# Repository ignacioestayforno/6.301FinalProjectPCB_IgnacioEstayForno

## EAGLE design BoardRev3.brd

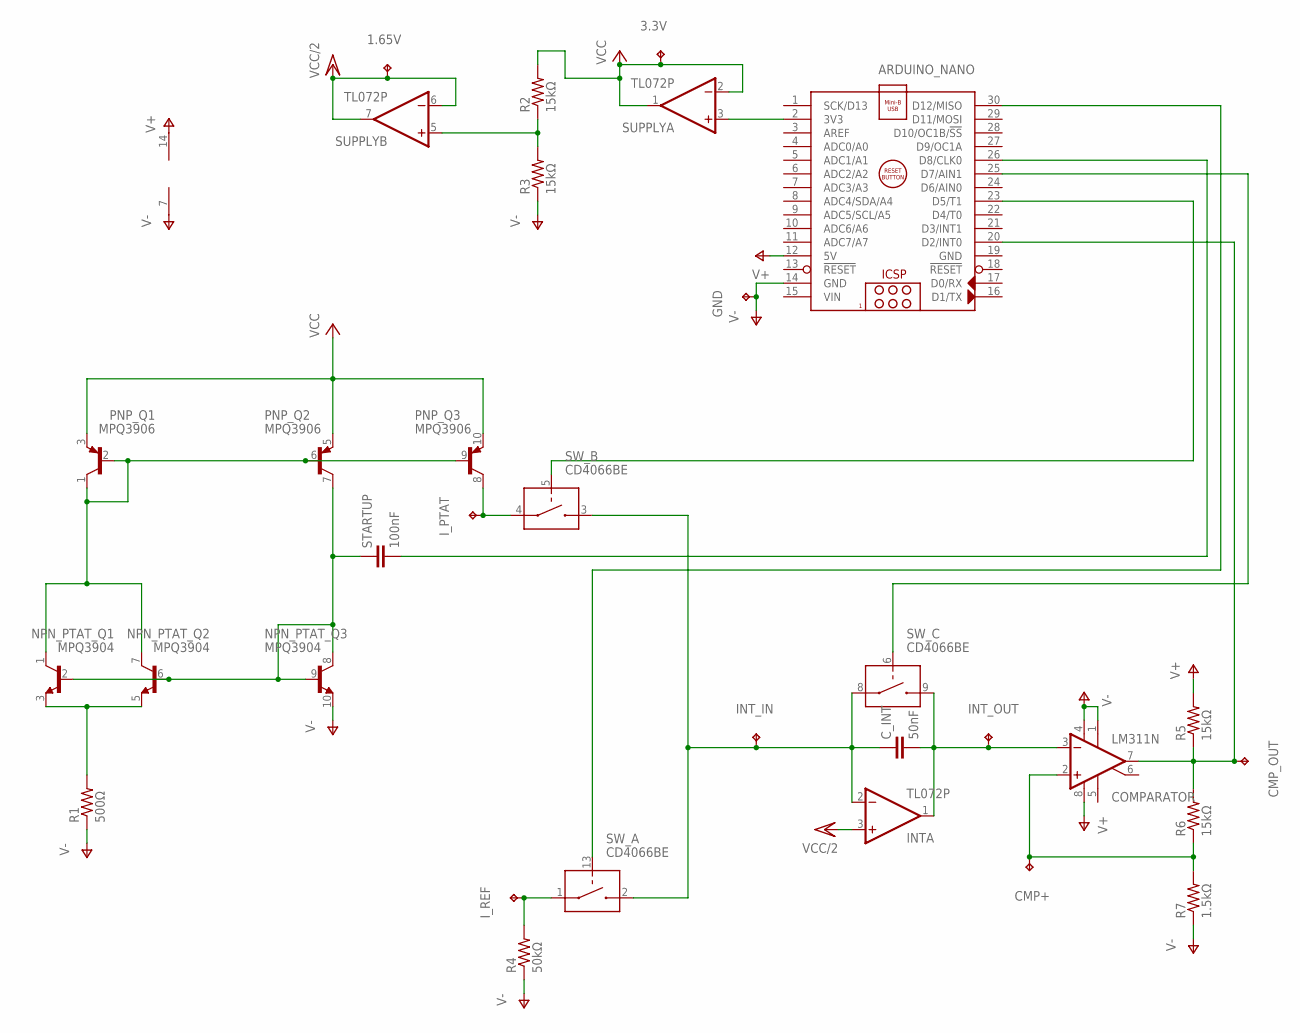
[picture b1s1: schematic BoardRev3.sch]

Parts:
1.65V, 3.3V: TESTPOINT; KEYSTONE_5000_MINIATURE
ARDUINO_NANO: ARDUINO_NANO
CMP+: TESTPOINT; KEYSTONE_5000_MINIATURE
CMP_OUT: TESTPOINT; KEYSTONE_5000_MINIATURE
COMPARATOR: LM311N; DIL08
C_INT: 50nF; C025-025X050
GND: TESTPOINT; KEYSTONE_5000_MINIATURE
INT: TL072P; DIL08
INT_IN: TESTPOINT; KEYSTONE_5000_MINIATURE
INT_OUT: TESTPOINT; KEYSTONE_5000_MINIATURE
I_PTAT: TESTPOINT; KEYSTONE_5000_MINIATURE
I_REF: TESTPOINT; KEYSTONE_5000_MINIATURE
NPN_PTAT: MPQ3904; DIL14
PNP: MPQ3906; DIL14
R1: 500Ω; 0207/10
R2, R3, R5, R6: 15kΩ; 0207/10
R4: 50kΩ; 0207/10
R7: 1.5kΩ; 0207/10
STARTUP: 100nF; C050-030X075
SUPPLY: TL072P; DIL08
SW: CD4066BE; DIL14

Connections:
+3V3: 3.3V.P$1, PNP.3 (E), PNP.5 (E), PNP.10 (E), R2.2, SUPPLY.1 (OUT), SUPPLY.2 (-IN)
GND: ARDUINO_NANO.19 (GND)
unnamed: ARDUINO_NANO.26 (D8/CLK0), STARTUP.2
unnamed: NPN_PTAT.1 (C), NPN_PTAT.7 (C), PNP.1 (C), PNP.2 (B), PNP.6 (B), PNP.9 (B)
unnamed: NPN_PTAT.3 (E), NPN_PTAT.5 (E), R1.2
unnamed: ARDUINO_NANO.2 (3V3), SUPPLY.3 (+IN)
unnamed: NPN_PTAT.2 (B), NPN_PTAT.6 (B), NPN_PTAT.8 (C), NPN_PTAT.9 (B), PNP.7 (C), STARTUP.1
unnamed: CMP+.P$1, COMPARATOR.2 (+IN), R6.1, R7.2
unnamed: R2.1, R3.2, SUPPLY.5 (+IN)
unnamed: ARDUINO_NANO.20 (D2/INT0), CMP_OUT.P$1, COMPARATOR.7 (OUT), R5.1, R6.2
unnamed: C_INT.1, INT.2 (-IN), INT_IN.P$1, SW.2 (IN/OUT2), SW.3 (IN/OUT2), SW.8 (IN/OUT1)
unnamed: COMPARATOR.3 (-IN), C_INT.2, INT.1 (OUT), INT_OUT.P$1, SW.9 (IN/OUT2)
unnamed: I_PTAT.P$1, PNP.8 (C), SW.4 (IN/OUT1)
unnamed: ARDUINO_NANO.30 (D12/MISO), SW.13 (CONTROL)
unnamed: I_REF.P$1, R4.2, SW.1 (IN/OUT1)
unnamed: ARDUINO_NANO.23 (D5/T1), SW.5 (CONTROL)
unnamed: ARDUINO_NANO.25 (D7/AIN1), SW.6 (CONTROL)
V+: ARDUINO_NANO.12 (5V), COMPARATOR.8 (V+), INT.8 (V+), R5.2, SUPPLY.8 (V+), SW.14 (V+)
V-: ARDUINO_NANO.14 (GND), COMPARATOR.1 (GND), COMPARATOR.4 (V-), GND.P$1, INT.4 (V-), NPN_PTAT.10 (E), R1.1, R3.1, R4.1, R7.1, SUPPLY.4 (V-), SW.7 (V-)
VCC/2: 1.65V.P$1, INT.3 (+IN), SUPPLY.6 (-IN), SUPPLY.7 (OUT)
VIN: ARDUINO_NANO.15 (VIN)

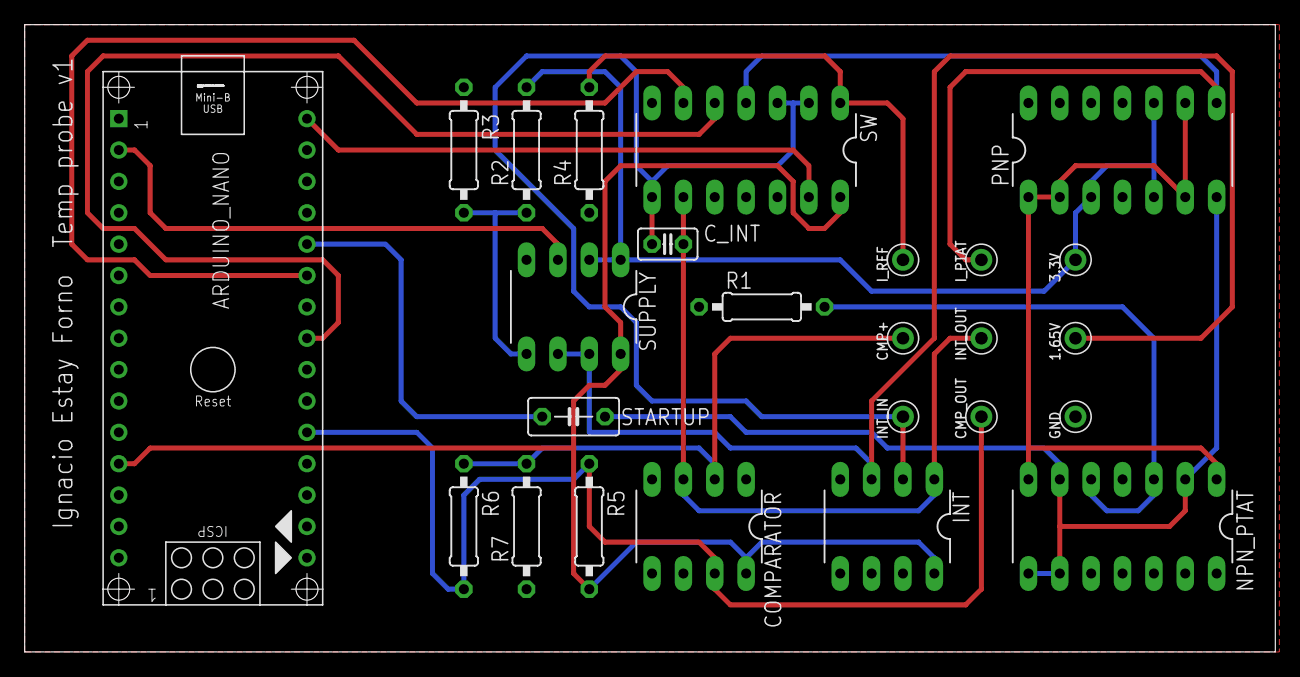
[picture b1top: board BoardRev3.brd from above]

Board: 2 copper layers, 101.3 x 50.8 mm, 25 parts (0 on the bottom side), 19 nets.

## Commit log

2016-12-09 :lollipop: Added .gitattributes & .gitignore files
2016-12-09 6.301 Board files
2016-12-09 Renaming
